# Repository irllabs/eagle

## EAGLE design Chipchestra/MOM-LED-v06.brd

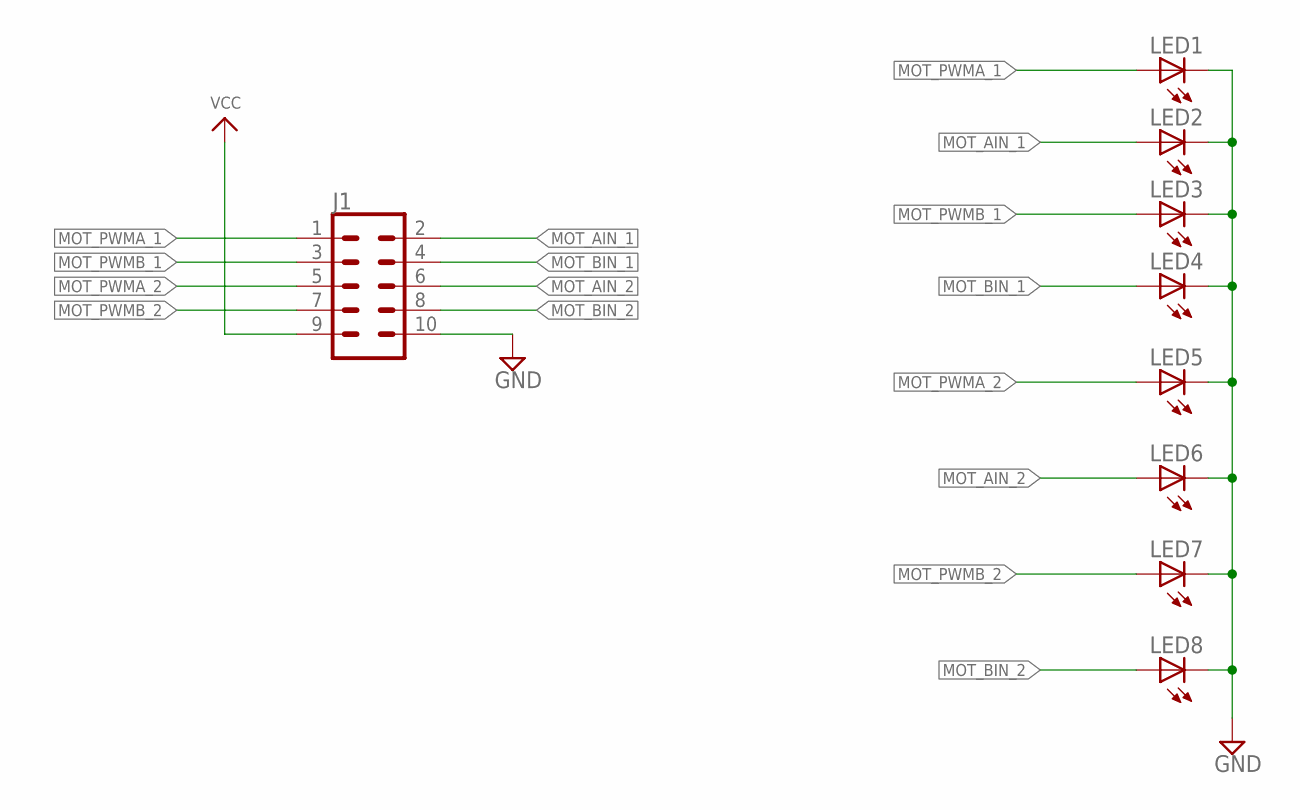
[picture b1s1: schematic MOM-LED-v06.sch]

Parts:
J1: CONN_05X2SHD_LOCK; 2X5-SHROUDED_LOCK
LED1, LED2, LED3, LED4, LED5, LED6, LED7, LED8: LED5MM

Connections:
GND: J1.10, LED1.K (C), LED2.K (C), LED3.K (C), LED4.K (C), LED5.K (C), LED6.K (C), LED7.K (C), LED8.K (C)
MOT_AIN_1: J1.2, LED2.A
MOT_AIN_2: J1.6, LED6.A
MOT_BIN_1: J1.4, LED4.A
MOT_BIN_2: J1.8, LED8.A
MOT_PWMA_1: J1.1, LED1.A
MOT_PWMA_2: J1.5, LED5.A
MOT_PWMB_1: J1.3, LED3.A
MOT_PWMB_2: J1.7, LED7.A
VCC: J1.9

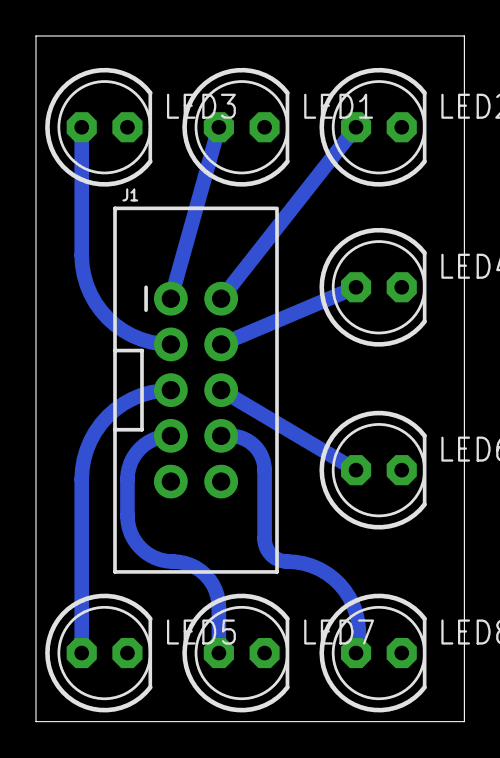
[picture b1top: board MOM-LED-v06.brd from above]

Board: 2 copper layers, 23.8 x 38.1 mm, 9 parts (0 on the bottom side), 9 nets.

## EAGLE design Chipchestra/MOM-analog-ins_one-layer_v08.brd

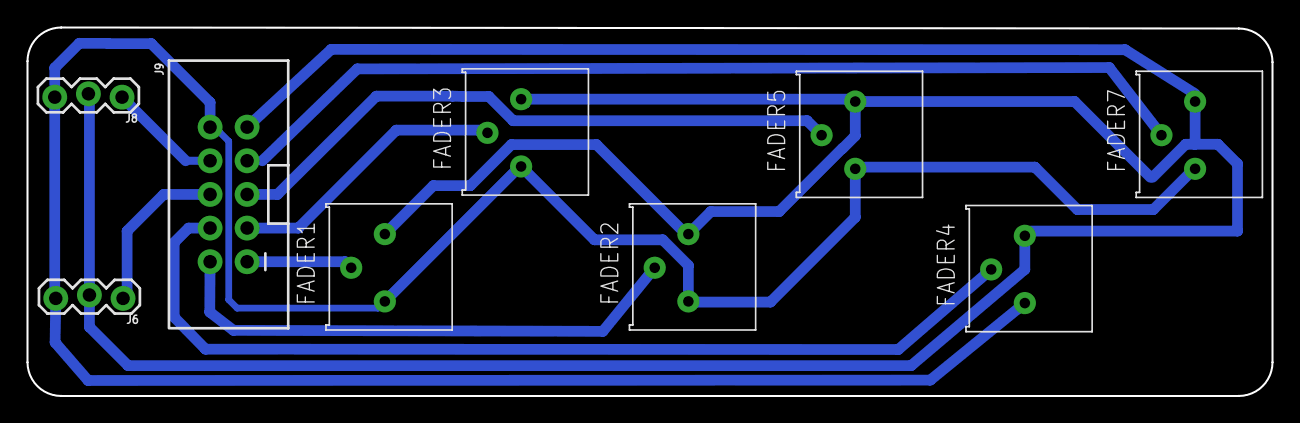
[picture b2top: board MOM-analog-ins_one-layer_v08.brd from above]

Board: 2 copper layers, 94.0 x 27.8 mm, 9 parts (0 on the bottom side), 10 nets.

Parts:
FADER1, FADER2, FADER3, FADER4, FADER5, FADER7: TRIMPOT-DIGIKEY
J6, J8: 1X03_LOCK
J9: 2X5-SHROUDED_LOCK

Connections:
ANALOG1: FADER1.2, J9.1
ANALOG2: FADER2.2, J9.2
ANALOG3: FADER3.2, J9.3
ANALOG4: FADER4.2, J9.4
ANALOG5: FADER5.2, J9.5
ANALOG6: J6.1, J9.6
ANALOG7: FADER7.2, J9.7
ANALOG8: J8.1, J9.8
GND: FADER1.3, FADER2.3, FADER3.3, FADER4.3, FADER5.3, FADER7.3, J6.3, J8.3, J9.10
VCC: FADER1.1, FADER2.1, FADER3.1, FADER4.1, FADER5.1, FADER7.1, J6.2, J8.2, J9.9

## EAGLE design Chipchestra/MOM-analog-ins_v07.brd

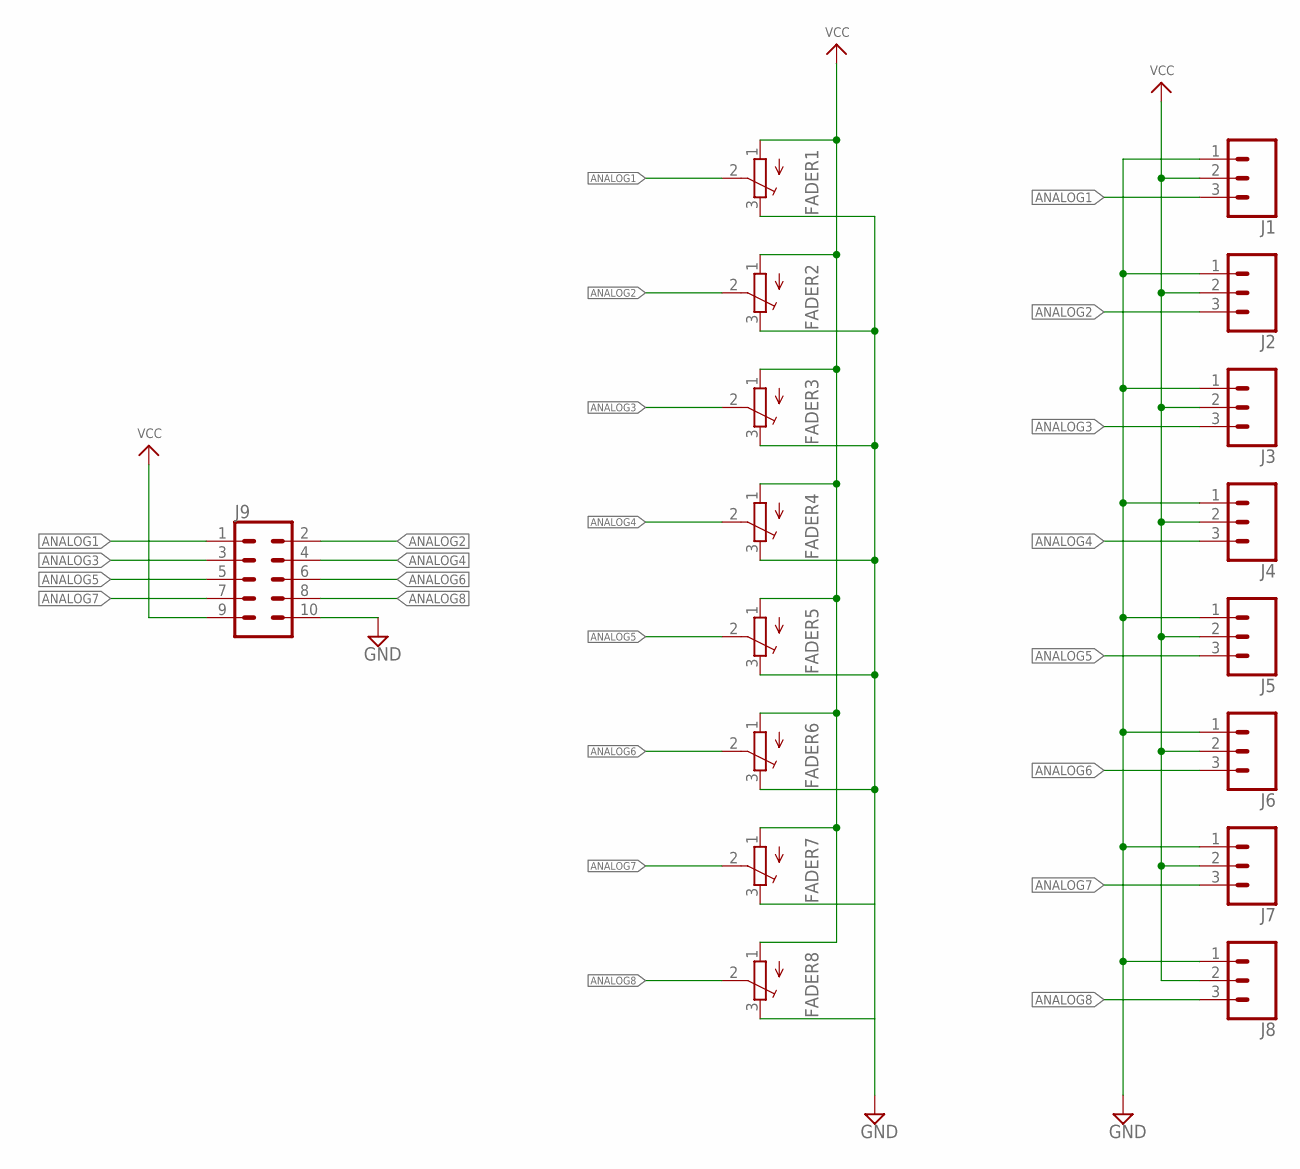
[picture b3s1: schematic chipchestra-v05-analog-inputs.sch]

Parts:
FADER1, FADER2, FADER3, FADER4, FADER5, FADER6, FADER7, FADER8: TRIMPOT3386; TRIM-3386
J1, J2, J3, J4, J5, J6, J7, J8: CONN_03LOCK; 1X03_LOCK
J9: CONN_05X2SHD_LOCK; 2X5-SHROUDED_LOCK

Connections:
ANALOG1: FADER1.2 (S), J1.3, J9.1
ANALOG2: FADER2.2 (S), J2.3, J9.2
ANALOG3: FADER3.2 (S), J3.3, J9.3
ANALOG4: FADER4.2 (S), J4.3, J9.4
ANALOG5: FADER5.2 (S), J5.3, J9.5
ANALOG6: FADER6.2 (S), J6.3, J9.6
ANALOG7: FADER7.2 (S), J7.3, J9.7
ANALOG8: FADER8.2 (S), J8.3, J9.8
GND: FADER1.3 (E), FADER2.3 (E), FADER3.3 (E), FADER4.3 (E), FADER5.3 (E), FADER6.3 (E), FADER7.3 (E), FADER8.3 (E), J1.1, J2.1, J3.1, J4.1, J5.1, J6.1, J7.1, J8.1, J9.10
VCC: FADER1.1 (A), FADER2.1 (A), FADER3.1 (A), FADER4.1 (A), FADER5.1 (A), FADER6.1 (A), FADER7.1 (A), FADER8.1 (A), J1.2, J2.2, J3.2, J4.2, J5.2, J6.2, J7.2, J8.2, J9.9

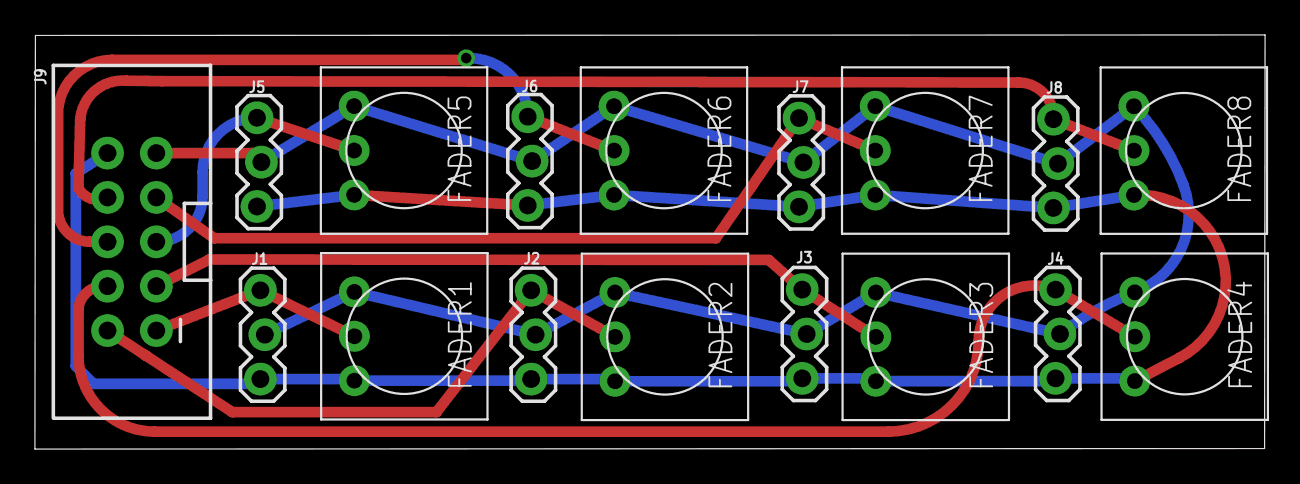
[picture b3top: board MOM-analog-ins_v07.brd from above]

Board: 2 copper layers, 70.4 x 23.7 mm, 17 parts (0 on the bottom side), 10 nets.

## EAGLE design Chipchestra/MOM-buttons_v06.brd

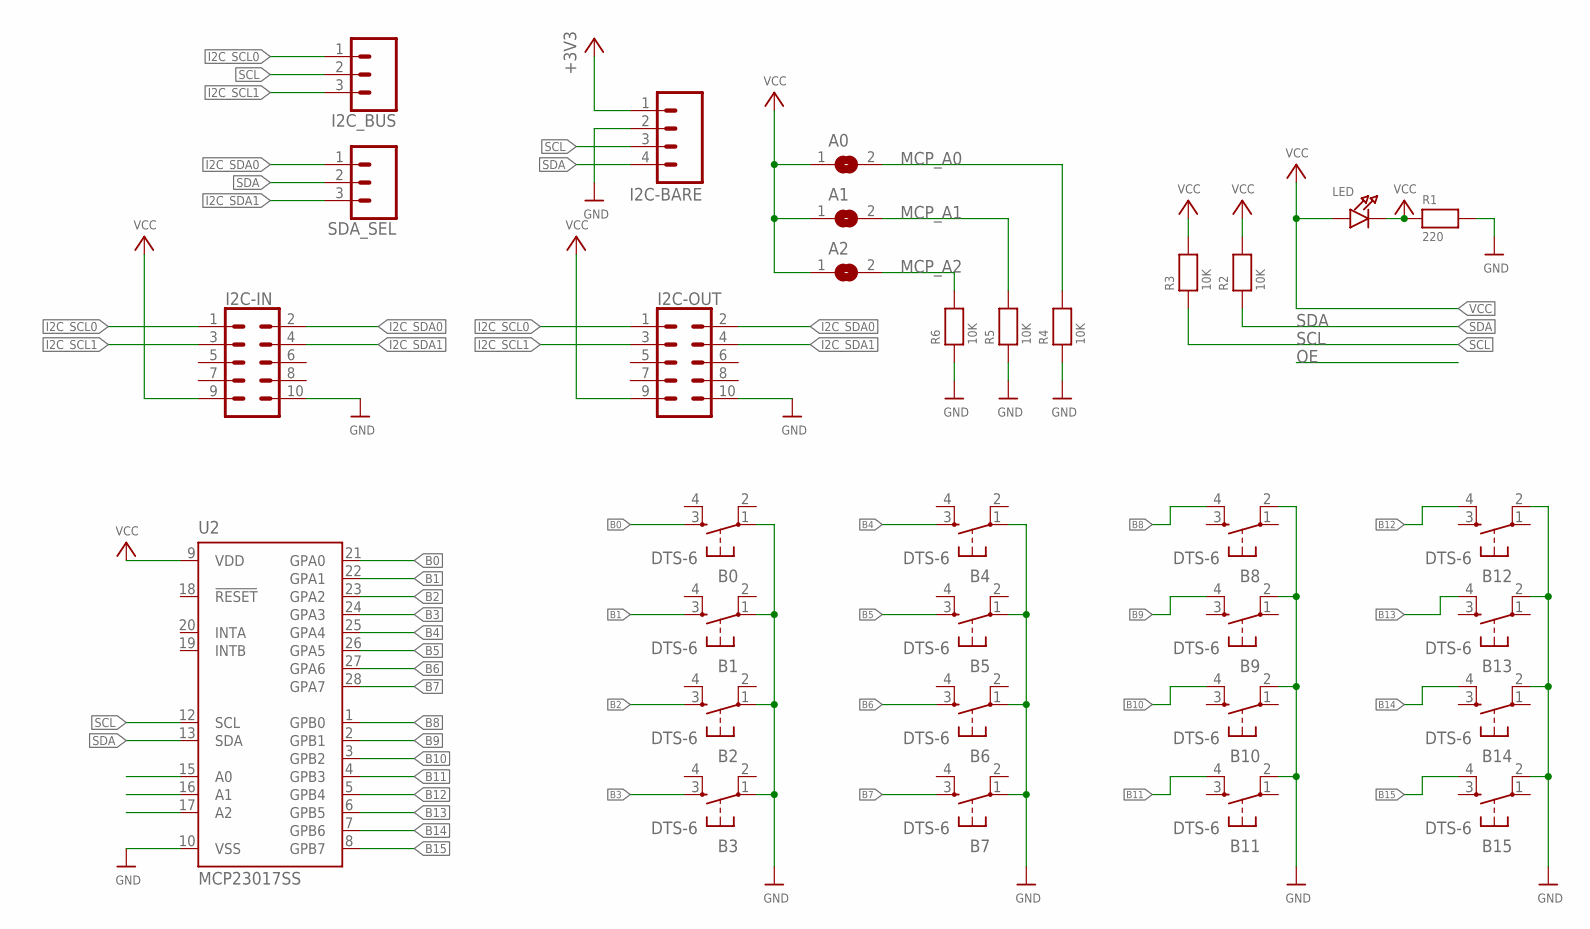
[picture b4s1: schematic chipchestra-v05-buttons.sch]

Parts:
A0, A1, A2: SOLDERJUMPERREFLOW_NOPASTE; SOLDERJUMPER_REFLOW_NOPASTE
B0, B1, B2, B3, B4, B5, B6, B7, B8, B9, B10, B11, B12, B13, B14, B15: DTS-6
I2C-BARE: M04LOCK; 1X04_LOCK
I2C-IN, I2C-OUT: CONN_05X2SHD_LOCK; 2X5-SHROUDED_LOCK
I2C_BUS: CONN_03LOCK; 1X03_LOCK
LED: LED0805; CHIPLED_0805
R1: 220; 0805
R2, R3, R4, R5, R6: 10K; 0805
SDA_SEL: CONN_03LOCK; 1X03_LOCK
U2: MCP23017SS; SSOP28

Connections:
+3V3: I2C-BARE.1
B0: B0.3, U2.21 (GPA0)
B1: B1.3, U2.22 (GPA1)
B2: B2.3, U2.23 (GPA2)
B3: B3.3, U2.24 (GPA3)
B4: B4.3, U2.25 (GPA4)
B5: B5.3, U2.26 (GPA5)
B6: B6.3, U2.27 (GPA6)
B7: B7.3, U2.28 (GPA7)
B8: B8.4, U2.1 (GPB0)
B9: B9.4, U2.2 (GPB1)
B10: B10.4, U2.3 (GPB2)
B11: B11.4, U2.4 (GPB3)
B12: B12.4, U2.5 (GPB4)
B13: B13.4, U2.6 (GPB5)
B14: B14.4, U2.7 (GPB6)
B15: B15.4, U2.8 (GPB7)
GND: B0.1, B1.1, B2.1, B3.1, B4.1, B5.1, B6.1, B7.1, B8.2, B9.2, B10.2, B11.2, B12.2, B13.2, B14.2, B15.2, I2C-BARE.2, I2C-IN.10, I2C-OUT.10, R1.2, R4.1, R5.1, R6.1, U2.10 (VSS)
I2C_SCL0: I2C-IN.1, I2C-OUT.1, I2C_BUS.1
I2C_SCL1: I2C-IN.3, I2C-OUT.3, I2C_BUS.3
I2C_SDA0: I2C-IN.2, I2C-OUT.2, SDA_SEL.1
I2C_SDA1: I2C-IN.4, I2C-OUT.4, SDA_SEL.3
MCP_A0: A0.2, R4.2, U2.15 (A0)
MCP_A1: A1.2, R5.2, U2.16 (A1)
MCP_A2: A2.2, R6.2, U2.17 (A2)
unnamed: LED.C, R1.1
SCL: I2C-BARE.3, I2C_BUS.2, R3.1, U2.12 (SCL)
SDA: I2C-BARE.4, R2.1, SDA_SEL.2, U2.13 (SDA)
VCC: A0.1, A1.1, A2.1, I2C-IN.9, I2C-OUT.9, LED.A, R2.2, R3.2, U2.9 (VDD)

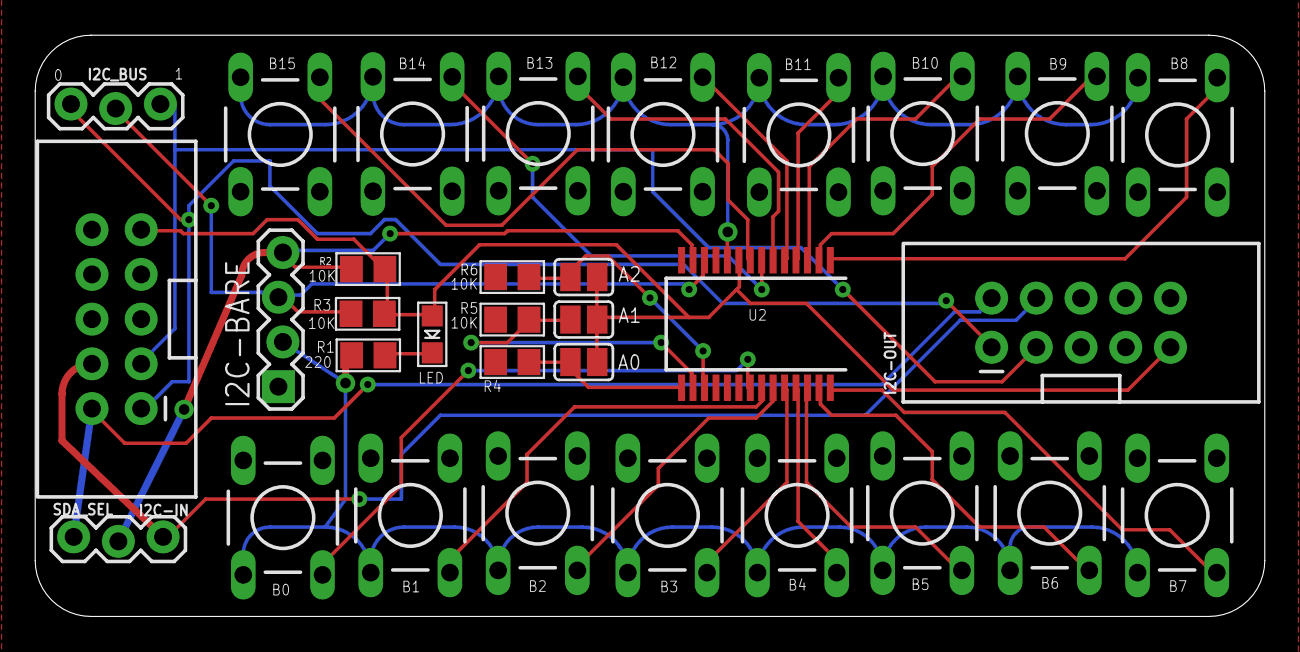
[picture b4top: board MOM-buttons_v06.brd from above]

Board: 2 copper layers, 69.8 x 33.0 mm, 32 parts (0 on the bottom side), 28 nets.

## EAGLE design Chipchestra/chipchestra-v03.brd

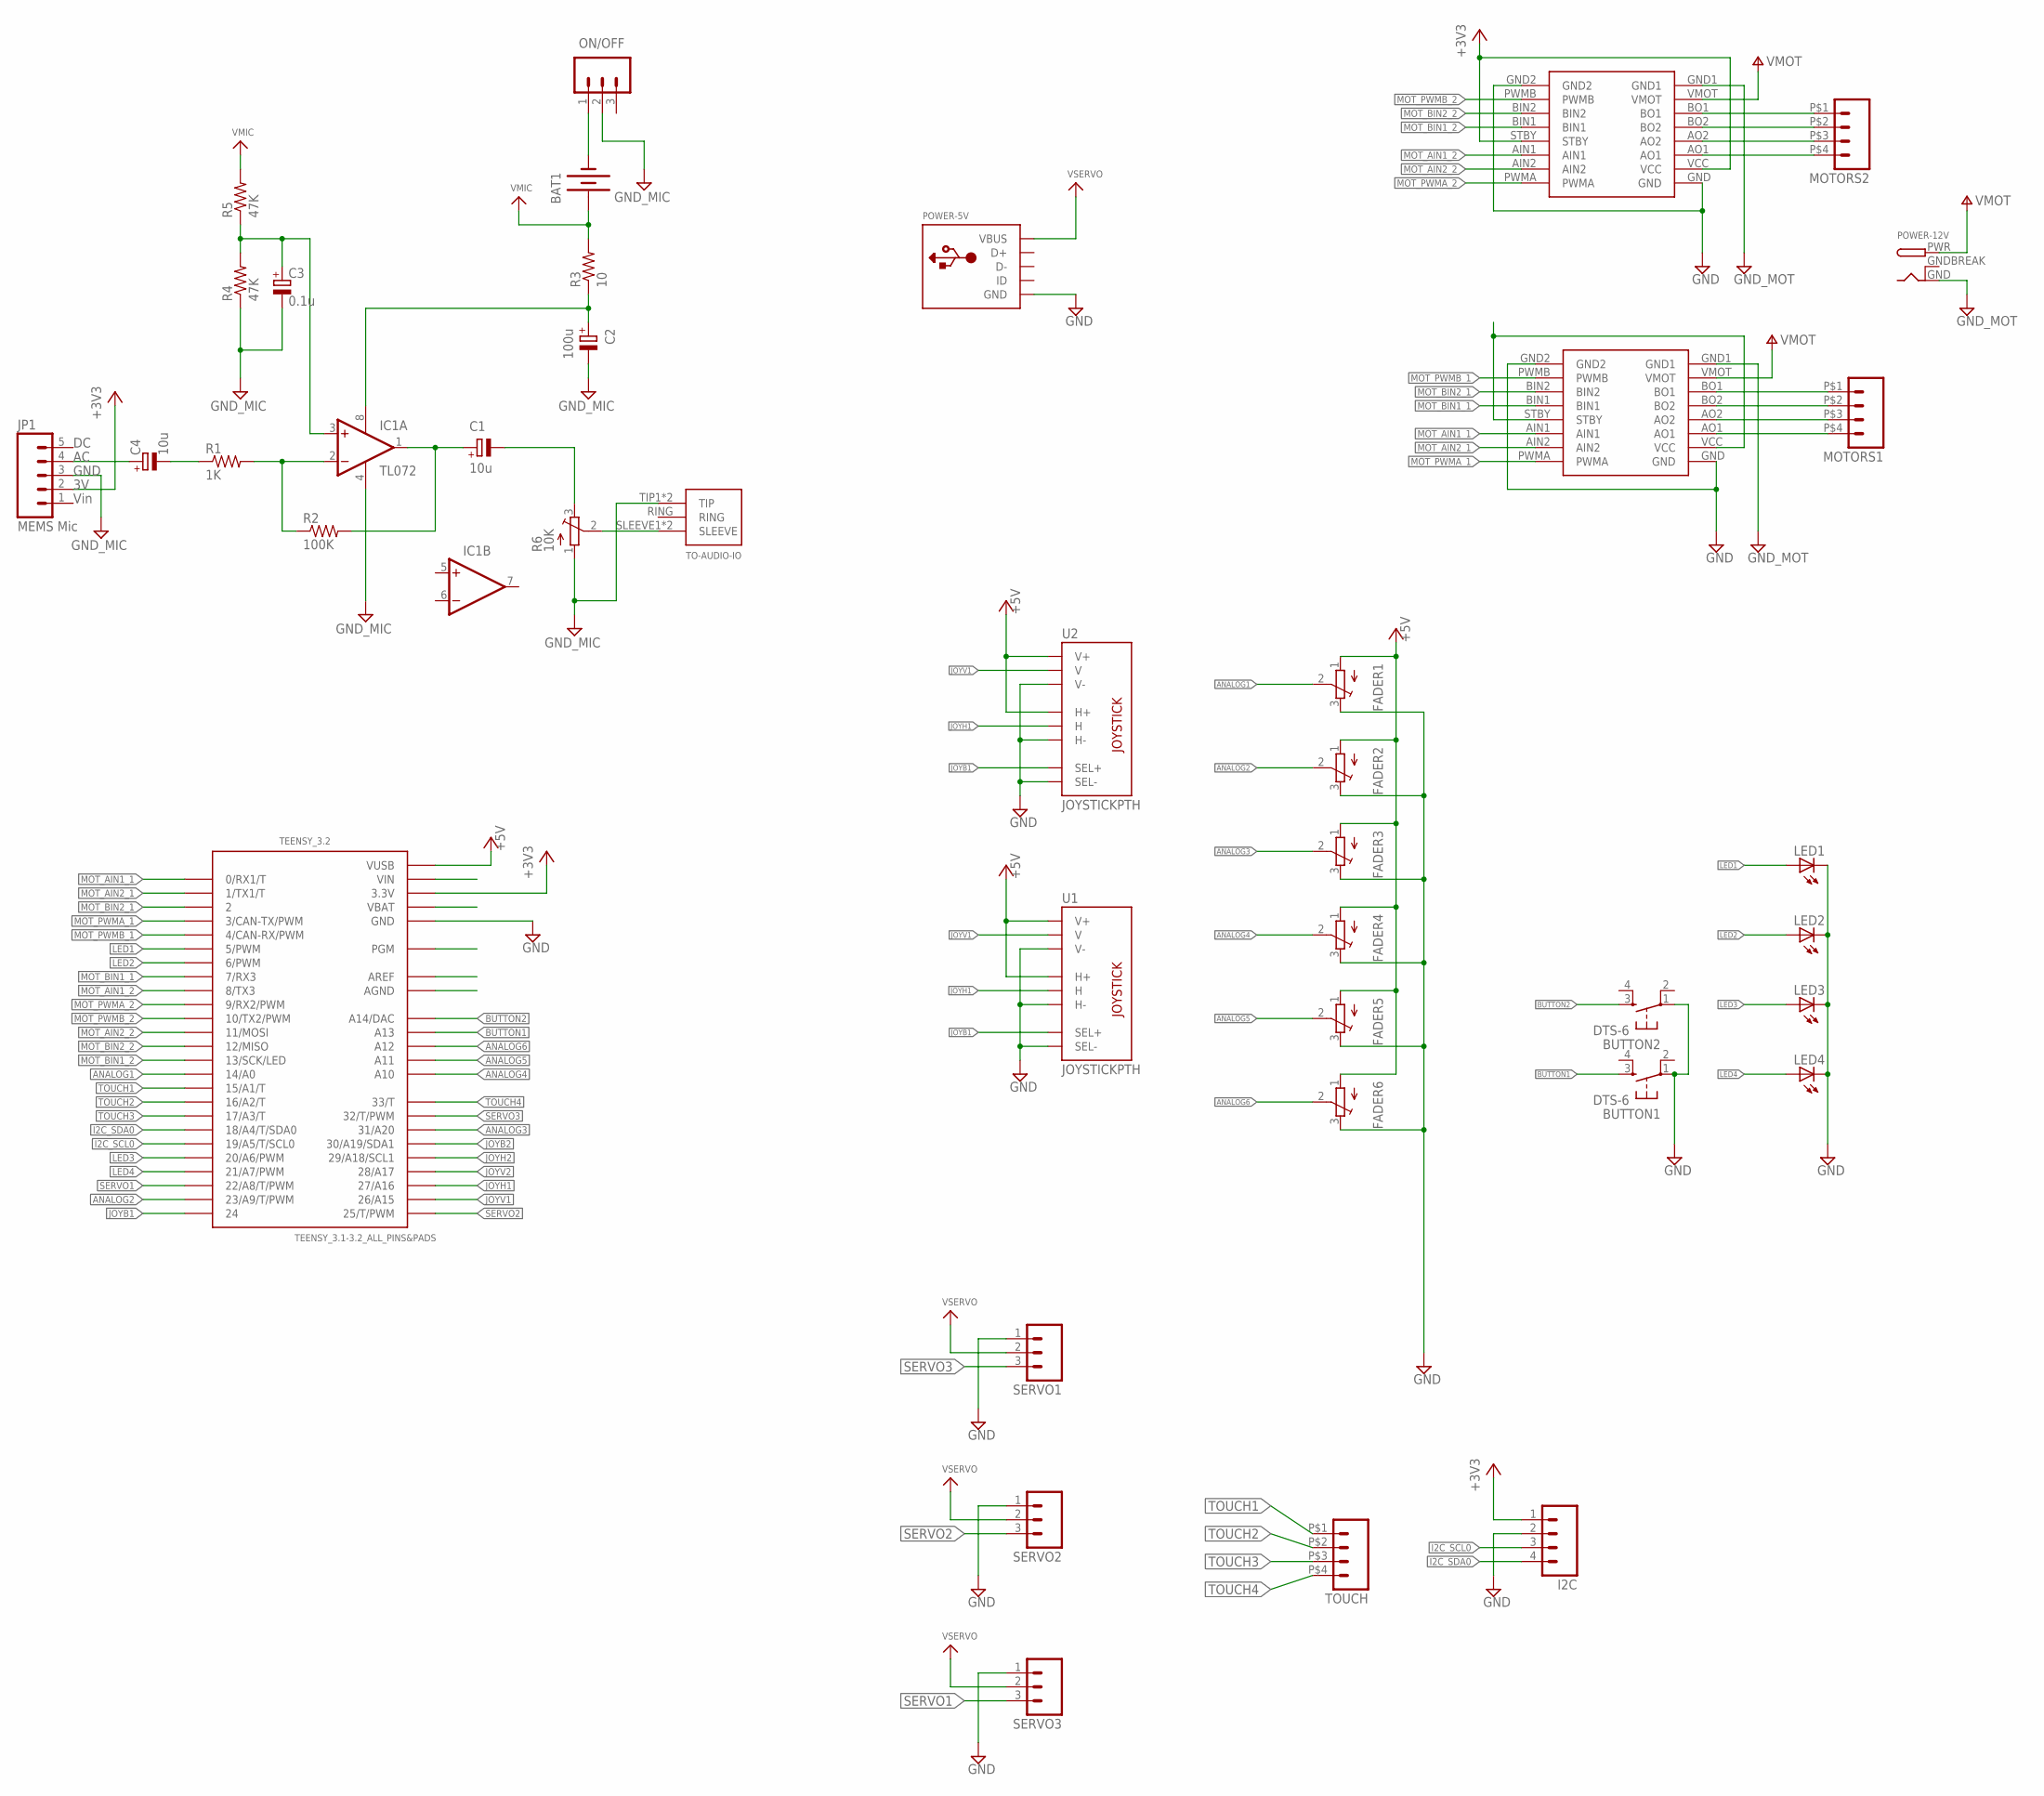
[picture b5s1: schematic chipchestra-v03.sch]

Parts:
BAT1: BATTERYA23; BATTERY-A23
BUTTON1, BUTTON2: DTS-6
C1, C4: 10u; E2,5-5
C2: 100u; E2,5-5
C3: 0.1u; E2,5-5
FADER1, FADER2, FADER3, FADER4, FADER5, FADER6: TRIMPOT3386; TRIM-3386
I2C: M04LOCK; 1X04_LOCK
IC1: OPA2134PA; DIL08
JP1: MEMS Mic; 1X05_LOCK
LED1, LED2, LED3, LED4: LED3MM
MOTORS1, MOTORS2: M04; SPRINGTERMINAL-2.54MM-4
ON/OFF: labl; SPDT-SWITCH
POWER-5V: USBMICRO_20329; 4UCONN_20329
POWER-12V: DCBARRELPTH; DCJACK_2MM_PTH
R1: 1K; 0204/5
R2: 100K; 0204/5
R3: 10; 0204/5
R4, R5: 47K; 0204/5
R6: 10K; TRIM-3386
SERVO1, SERVO2, SERVO3: M03LOCK; 1X03_LOCK
TEENSY_3.2: TEENSY_3.1-3.2_ALL_PINS&PADS; TEENSY_3.0-3.2_ALL_PINS_&_PADS
TO-AUDIO-IO: 1/8"-F-STEREO-PCB
TOUCH: M04; SPRINGTERMINAL-2.54MM-4
U1, U2: JOYSTICKPTH; JOYSTICK
U$6, U$7: POLOLU_TB6612FNG

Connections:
+3V3: I2C.1, JP1.2, TEENSY_3.2.3.3V, TEENSY_3.2.3.3V1 (3.3V), TEENSY_3.2.3.3V2 (3.3V), U$6.STBY, U$6.VCC
+5V: FADER1.1 (A), FADER2.1 (A), FADER3.1 (A), FADER4.1 (A), FADER5.1 (A), FADER6.1 (A), TEENSY_3.2.VUSB, U1.H1 (H+), U1.V1 (V+), U2.H1 (H+), U2.V1 (V+)
ANALOG1: FADER1.2 (S), TEENSY_3.2.14/A0
ANALOG2: FADER2.2 (S), TEENSY_3.2.23/A9 (23/A9/T/PWM)
ANALOG3: FADER3.2 (S), TEENSY_3.2.31 (31/A20)
ANALOG4: FADER4.2 (S), TEENSY_3.2.A10
ANALOG5: FADER5.2 (S), TEENSY_3.2.A11
ANALOG6: FADER6.2 (S), TEENSY_3.2.A12
BUTTON1: BUTTON1.3, TEENSY_3.2.A13
BUTTON2: BUTTON2.3, TEENSY_3.2.RESET/DAC (A14/DAC)
GND: BUTTON1.1, BUTTON2.1, FADER1.3 (E), FADER2.3 (E), FADER3.3 (E), FADER4.3 (E), FADER5.3 (E), FADER6.3 (E), I2C.2, LED1.K (C), LED2.K (C), LED3.K (C), LED4.K (C), POWER-5V.BASE@1 (GND), POWER-5V.BASE@2 (GND), POWER-5V.GND, POWER-5V.SPRT@1 (GND), POWER-5V.SPRT@2 (GND), POWER-5V.SPRT@3 (GND), POWER-5V.SPRT@4 (GND), SERVO1.1, SERVO2.1, SERVO3.1, TEENSY_3.2.GND, TEENSY_3.2.GND1 (GND), TEENSY_3.2.GND2 (GND), U1.B2A (SEL-), U1.H3 (H-), U1.V3 (V-), U2.B2A (SEL-), U2.H3 (H-), U2.V3 (V-), U$6.GND, U$6.GND2, U$7.GND, U$7.GND2
GNDBREAK: POWER-12V.GNDBREAK
GND_MIC: C2.-, C3.-, IC1.4 (V-), JP1.3, R4.1, R6.1 (A), TO-AUDIO-IO.TIP1 (TIP), TO-AUDIO-IO.TIP2 (TIP)
GND_MOT: POWER-12V.GND, U$6.GND1, U$7.GND1
I2C_SCL0: I2C.3, TEENSY_3.2.19/A5 (19/A5/T/SCL0)
I2C_SDA0: I2C.4, TEENSY_3.2.18/A4 (18/A4/T/SDA0)
JOYB1: TEENSY_3.2.24, U1.B1A (SEL+), U2.B1A (SEL+)
JOYB2: TEENSY_3.2.30 (30/A19/SDA1)
JOYH1: TEENSY_3.2.27 (27/A16), U1.H2 (H), U2.H2 (H)
JOYH2: TEENSY_3.2.29 (29/A18/SCL1)
JOYV1: TEENSY_3.2.26 (26/A15), U1.V2 (V), U2.V2 (V)
JOYV2: TEENSY_3.2.28 (28/A17)
LED1: LED1.A, TEENSY_3.2.5 (5/PWM)
LED2: LED2.A, TEENSY_3.2.6 (6/PWM)
LED3: LED3.A, TEENSY_3.2.20/A6 (20/A6/PWM)
LED4: LED4.A, TEENSY_3.2.21/A7 (21/A7/PWM)
MOT_AIN1_1: TEENSY_3.2.0 (0/RX1/T), U$7.AIN1
MOT_AIN1_2: TEENSY_3.2.8 (8/TX3), U$6.AIN1
MOT_AIN2_1: TEENSY_3.2.1 (1/TX1/T), U$7.AIN2
MOT_AIN2_2: TEENSY_3.2.11 (11/MOSI), U$6.AIN2
MOT_BIN1_1: TEENSY_3.2.7 (7/RX3), U$7.BIN1
MOT_BIN1_2: TEENSY_3.2.13 (13/SCK/LED), U$6.BIN1
MOT_BIN2_1: TEENSY_3.2.2, U$7.BIN2
MOT_BIN2_2: TEENSY_3.2.12 (12/MISO), U$6.BIN2
MOT_PWMA_1: TEENSY_3.2.3 (3/CAN-TX/PWM), U$7.PWMA
MOT_PWMA_2: TEENSY_3.2.9 (9/RX2/PWM), U$6.PWMA
MOT_PWMB_1: TEENSY_3.2.4 (4/CAN-RX/PWM), U$7.PWMB
MOT_PWMB_2: TEENSY_3.2.10 (10/TX2/PWM), U$6.PWMB
unnamed: C2.+, IC1.8 (V+), R3.1
unnamed: BAT1.GND@1 (-), ON/OFF.1
unnamed: C4.+, JP1.4
unnamed: C4.-, R1.1
unnamed: IC1.2 (-IN), R1.2, R2.1
unnamed: C1.-, R6.3 (E)
unnamed: R6.2 (S), TO-AUDIO-IO.SLEEVE1 (SLEEVE), TO-AUDIO-IO.SLEEVE2 (SLEEVE)
unnamed: C3.+, IC1.3 (+IN), R4.2, R5.1
unnamed: C1.+, IC1.1 (OUT), R2.2
unnamed: U$7.STBY, U$7.VCC
unnamed: MOTORS1.P$1 (1), U$7.BO1
unnamed: MOTORS1.P$2 (2), U$7.BO2
unnamed: MOTORS1.P$3 (3), U$7.AO2
unnamed: MOTORS1.P$4 (4), U$7.AO1
unnamed: MOTORS2.P$1 (1), U$6.BO1
unnamed: MOTORS2.P$2 (2), U$6.BO2
unnamed: MOTORS2.P$3 (3), U$6.AO2
unnamed: MOTORS2.P$4 (4), U$6.AO1
SERVO1: SERVO3.3, TEENSY_3.2.22/A8 (22/A8/T/PWM)
SERVO2: SERVO2.3, TEENSY_3.2.25 (25/T/PWM)
SERVO3: SERVO1.3, TEENSY_3.2.32 (32/T/PWM)
TOUCH1: TEENSY_3.2.15/A1 (15/A1/T), TOUCH.P$1 (1)
TOUCH2: TEENSY_3.2.16/A2 (16/A2/T), TOUCH.P$2 (2)
TOUCH3: TEENSY_3.2.17/A3 (17/A3/T), TOUCH.P$3 (3)
TOUCH4: TEENSY_3.2.33 (33/T), TOUCH.P$4 (4)
VBAT: SERVO1.2, SERVO2.2, SERVO3.2
VMIC: BAT1.PWR@1 (+), R3.2, R5.2
VMOT: POWER-12V.PWR, U$6.VMOT, U$7.VMOT

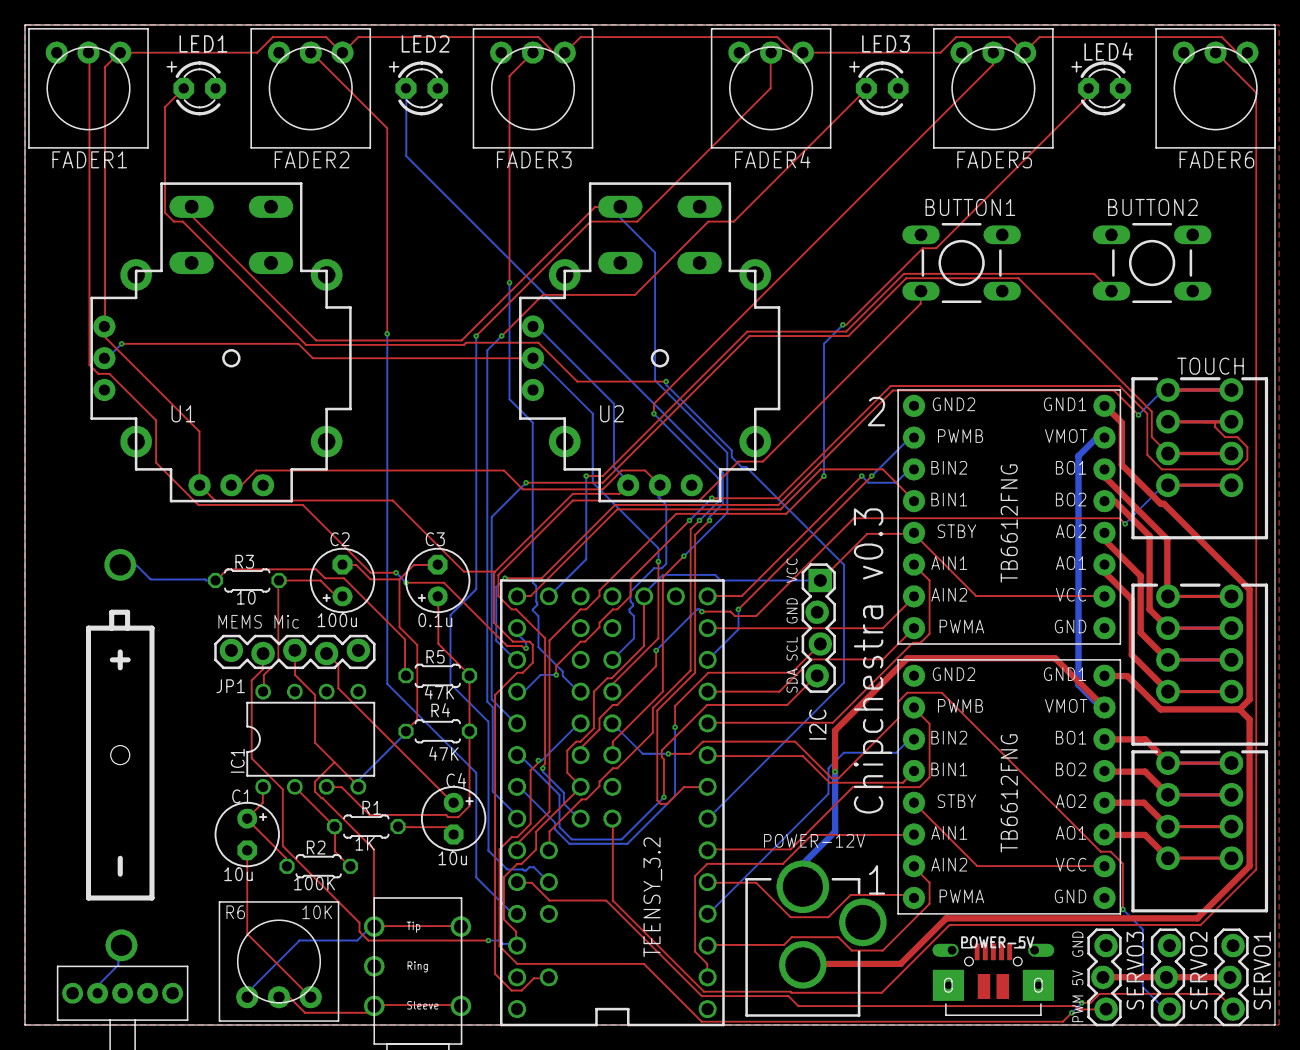
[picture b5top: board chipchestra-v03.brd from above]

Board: 2 copper layers, 100.0 x 80.0 mm, 41 parts (0 on the bottom side), 62 nets.

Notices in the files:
parts and their libraries:
SparkFun-Connectors: Licensing: Creative Commons ShareAlike 4.0 International - https://creativecommons.org/licenses/by-sa/4.0
microbuilder: This work is placed in the public domain, and may be freely used for commercial and non-commercial work with the following conditions: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
